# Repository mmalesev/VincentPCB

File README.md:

PCB for a senior design project - a virtual assistant

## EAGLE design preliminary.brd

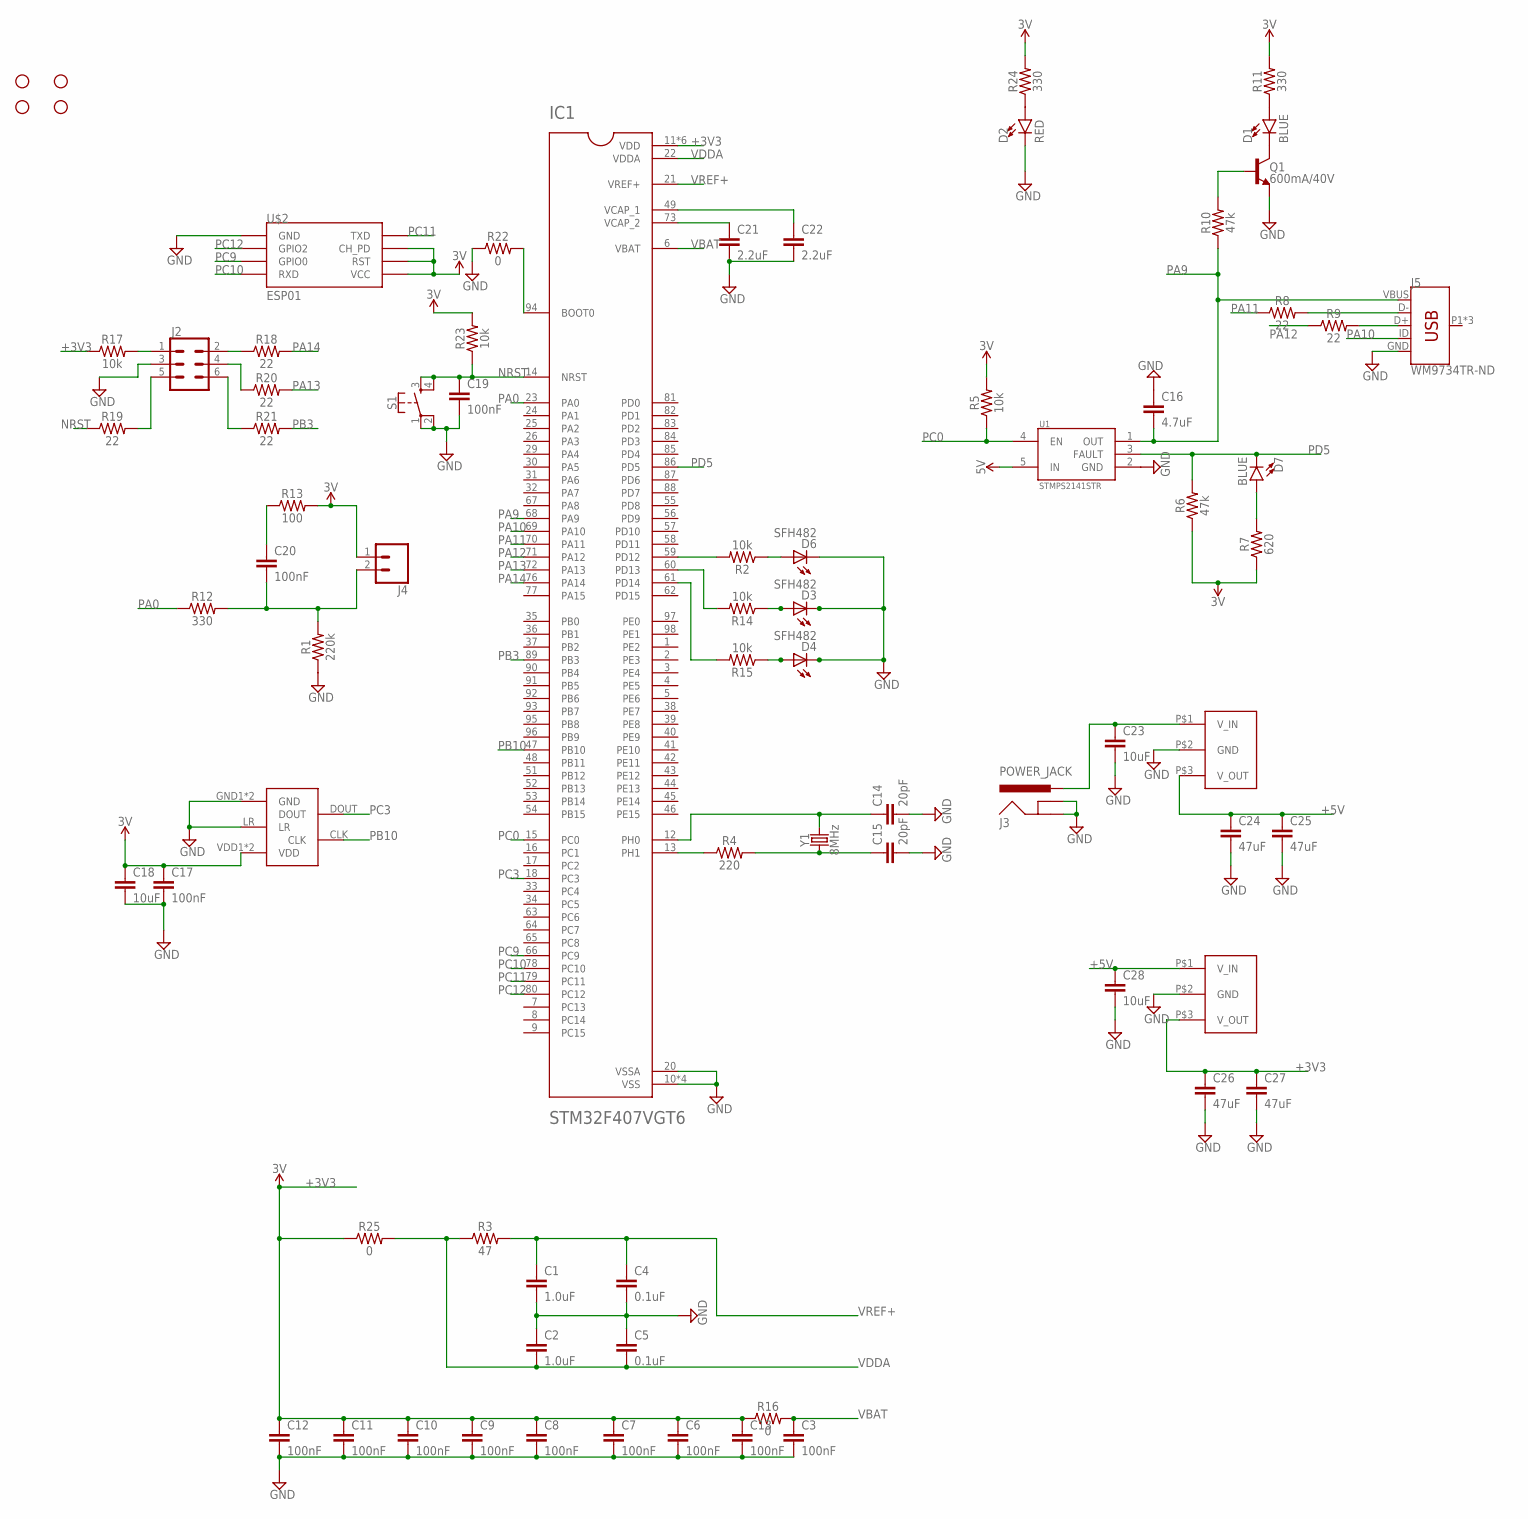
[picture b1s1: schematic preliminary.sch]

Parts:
C1, C2: 1.0uF; 0603
C3, C6, C7, C8, C9, C10, C11, C12, C13, C17, C19, C20: 100nF; 0603
C4, C5: 0.1uF; 0603
C14, C15: 20pF; 0603
C16: 4.7uF; 0603
C18, C23, C28: 10uF; 0603
C21, C22: 2.2uF; 0603
C24, C25, C26, C27: 47uF; 0603
D1, D7: BLUE; LED-0603
D2: RED; LED-0603
D3, D4, D6: SFH482
H1, H2, H3, H4: STAND-OFF
IC1: STM32F407VGT6; QFP50P1600X1600X160-100N
J2: CONN_03X2FEMALE_SMD; 2X3_SMD
J3: POWER_JACK; POWER_JACK_PTH
J4: CONN_02; 1X02
J5: WM9734TR-ND; USB-B-MICRO-SMD_VERT
Q1: 600mA/40V; SOT23-3
R1: 220k; 0603
R2, R5, R14, R15, R17, R23: 10k; 0603
R3: 47; 0603
R4: 220; 0603
R6, R10: 47k; 0603
R7: 620; 0603
R8, R9, R18, R19, R20, R21: 22; 0603
R11, R12, R24: 330; 0603
R13: 100; 0603
R16, R22, R25: 0; 0603
S1: MOMENTARY-SWITCH-SPST-2-SMD-4.6X2.8MM; TACTILE_SWITCH_SMD_4.6X2.8MM
U1: STMPS2141STR; SOT95P280X145-5N
U$2: ESP01
U$4: TPSM5; TO-220
U$5: TPSM3.3; TO-220
U$6: MP45DT02-M; HLGA
Y1: 8MHz; HC49US

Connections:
+3V3: C6.1, C7.1, C8.1, C9.1, C10.1, C11.1, C12.1, C13.1, C17.1, C18.1, C26.1, C27.1, IC1.11 (VDD), IC1.19 (VDD), IC1.28 (VDD), IC1.50 (VDD), IC1.75 (VDD), IC1.100 (VDD), J4.1, R5.2, R6.1, R7.1, R11.2, R13.2, R16.1, R17.1, R23.2, R24.2, R25.1, U$2.CH_PD, U$2.RST, U$2.VCC, U$5.P$3 (V_OUT), U$6.VDD1 (VDD), U$6.VDD2 (VDD)
+5V: C24.1, C25.1, C28.1, U1.5 (IN), U$4.P$3 (V_OUT), U$5.P$1 (V_IN)
GND: C1.2, C2.1, C3.2, C4.2, C5.1, C6.2, C7.2, C8.2, C9.2, C10.2, C11.2, C12.2, C13.2, C14.2, C15.2, C16.1, C17.2, C18.2, C19.2, C21.2, C22.2, C23.2, C24.2, C25.2, C26.2, C27.2, C28.2, D2.C, D3.K (C), D4.K (C), D6.K (C), IC1.10 (VSS), IC1.20 (VSSA), IC1.27 (VSS), IC1.74 (VSS), IC1.99 (VSS), J2.3, J3.GND, J3.GNDBREAK, J5.GND, Q1.2 (E), R1.1, R22.1, S1.1, S1.2, U1.2 (GND), U$2.GND, U$4.P$2 (GND), U$5.P$2 (GND), U$6.GND1 (GND), U$6.GND2 (GND), U$6.LR
unnamed: IC1.13 (PH1), R4.1
unnamed: C15.1, R4.2, Y1.1
unnamed: C14.1, IC1.12 (PH0), Y1.2
unnamed: C20.2, J4.2, R1.2, R12.2
unnamed: D7.A, R7.2
unnamed: J5.D-, R8.2
unnamed: J5.D+, R9.2
unnamed: Q1.1 (B), R10.2
unnamed: D1.C, Q1.3 (C)
unnamed: D1.A, R11.1
unnamed: D6.A, R2.1
unnamed: J2.2, R18.1
unnamed: IC1.61 (PD14), R15.2
unnamed: IC1.60 (PD13), R14.2
unnamed: C20.1, R13.1
unnamed: IC1.59 (PD12), R2.2
unnamed: D3.A, R14.1
unnamed: D4.A, R15.1
unnamed: C21.1, IC1.73 (VCAP_2)
unnamed: C22.1, IC1.49 (VCAP_1)
unnamed: J2.5, R19.2
unnamed: J2.1, R17.2
unnamed: C23.1, J3.PWR, U$4.P$1 (V_IN)
unnamed: J2.4, R20.1
unnamed: IC1.94 (BOOT0), R22.2
unnamed: J2.6, R21.1
unnamed: D2.A, R24.1
NRST: C19.1, IC1.14 (NRST), R19.1, R23.1, S1.3, S1.4
PA0: IC1.23 (PA0), R12.1
PA9: C16.2, IC1.68 (PA9), J5.VBUS, R10.1, U1.1 (OUT)
PA10: IC1.69 (PA10), J5.ID
PA11: IC1.70 (PA11), R8.1
PA12: IC1.71 (PA12), R9.1
PA13: IC1.72 (PA13), R20.2
PA14: IC1.76 (PA14), R18.2
PB3: IC1.89 (PB3), R21.2
PB10: IC1.47 (PB10), U$6.CLK
PC0: IC1.15 (PC0), R5.1, U1.4 (EN)
PC3: IC1.18 (PC3), U$6.DOUT
PC9: IC1.66 (PC9), U$2.GPIO0
PC10: IC1.78 (PC10), U$2.RX (RXD)
PC11: IC1.79 (PC11), U$2.TX (TXD)
PC12: IC1.80 (PC12), U$2.GPIO2
PD5: D7.C, IC1.86 (PD5), R6.2, U1.3 (FAULT)
VBAT: C3.1, IC1.6 (VBAT), R16.2
VDDA: C2.2, C5.2, IC1.22 (VDDA), R3.1, R25.2
VREF+: C1.1, C4.1, IC1.21 (VREF+), R3.2

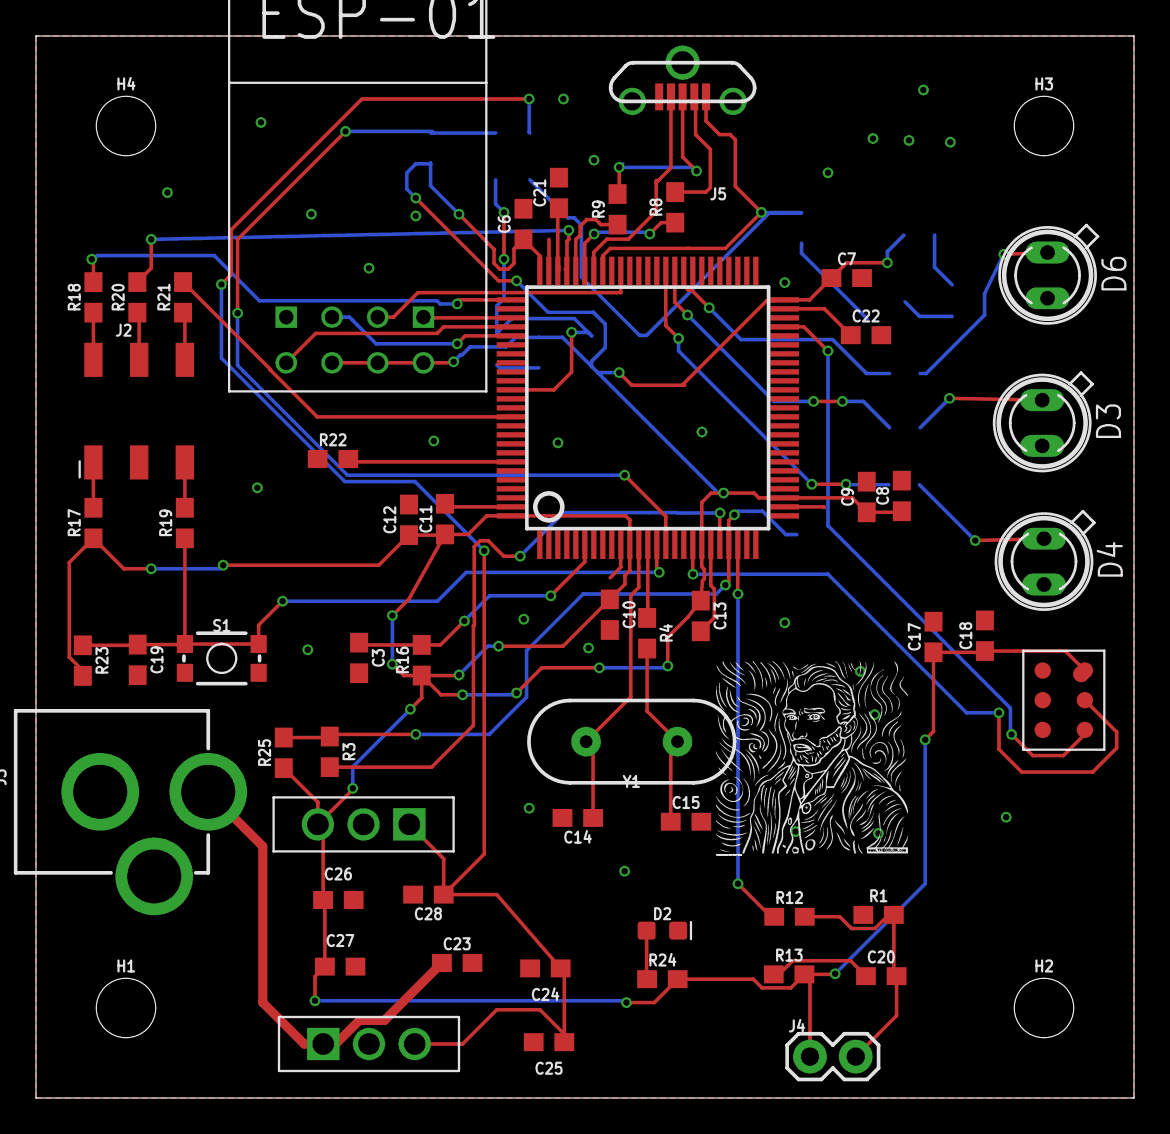
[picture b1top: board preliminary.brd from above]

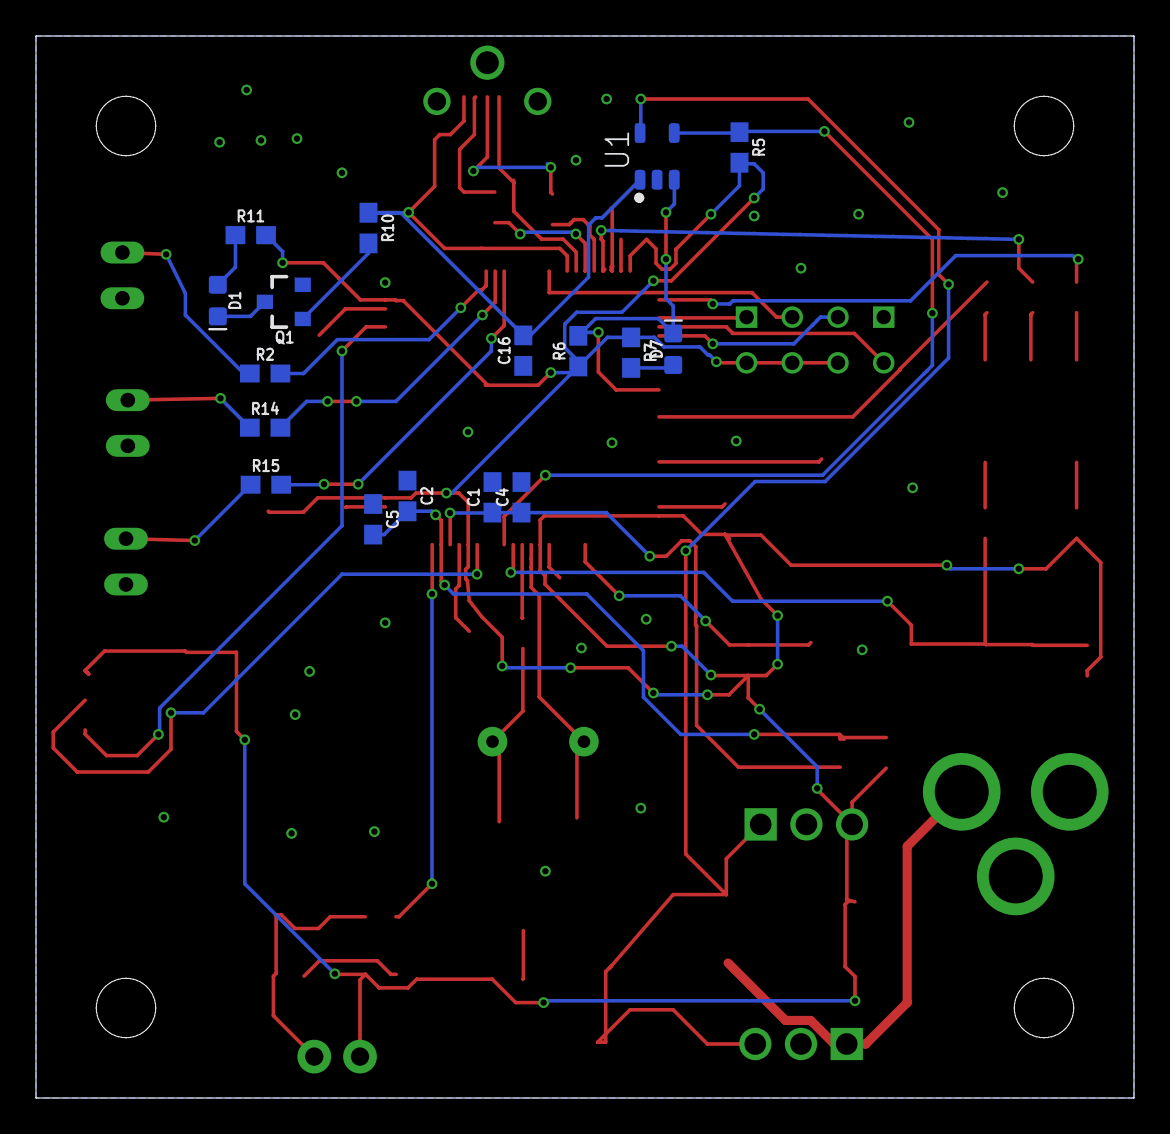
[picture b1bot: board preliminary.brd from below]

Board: 2 copper layers, 61.0 x 59.0 mm, 76 parts (17 on the bottom side), 50 nets.

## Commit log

2018-03-01 Review
2018-03-13 Schematic changed
2018-03-13 Placing components on the PCB
2018-03-14 2nd revision finished
2018-03-31 PCB as ordered
2018-04-17 Second round of PCBs

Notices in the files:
parts and their libraries:
SparkFun-Capacitors: Licensing: Creative Commons ShareAlike 4.0 International - https://creativecommons.org/licenses/by-sa/4.0
